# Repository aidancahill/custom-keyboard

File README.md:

# custom-keyboard

A 54-key split ergonomic keyboard with analog joysticks, shift register matrix scanning, and a Seeeduino XIAO nRF52840 BLE microcontroller. Designed from scratch using Ergogen, KiCad, and ZMK firmware.

## Features

- 54 Kailh Choc V1 low-profile keys with hotswap sockets
- Split ergonomic layout with column stagger and splay
- 2× analog joysticks (mouse movement + scroll)
- 74HC595 shift registers for column scanning (3× SIPO)
- 74HC165 shift register for row reading (1× PISO)
- Seeeduino XIAO nRF52840 BLE MCU
- 3D printed case with integrated bottom plate and heat-set inserts
- Custom Grogu silkscreen art

## Layout

```
Left half:                              Right half:
+---+---+---+---+---+---+              +---+---+---+---+---+---+
|Esc| 1 | 2 | 3 | 4 | 5 |              | 6 | 7 | 8 | 9 | 0 |Bks|
+---+---+---+---+---+---+              +---+---+---+---+---+---+
|Tab| Q | W | E | R | T |              | Y | U | I | O | P | \ |
+---+---+---+---+---+---+---+      +---+---+---+---+---+---+---+
| ` | A | S | D | F | G |Alt|      |Alt| H | J | K | L | ; | ' |
+---+---+---+---+---+---+---+      +---+---+---+---+---+---+---+
    | Z | X | C | V | B |              | N | M | , | . | / |
    +---+---+---+---+---+              +---+---+---+---+---+
            |Ctl|Shf|Spc|              |Fn |Shf|Ent|
            +---+---+---+              +---+---+---+

Fn Layer (hold Fn):
+---+---+---+---+---+---+              +---+---+---+---+---+---+
|F1 |F2 |F3 |F4 |F5 |F6 |              |F7 |F8 |F9 |F10|F11|F12|
+---+---+---+---+---+---+              +---+---+---+---+---+---+
| ~ | ! | @ | # | $ | % |              | ^ | & | * | ( | ) |Del|
+---+---+---+---+---+---+---+      +---+---+---+---+---+---+---+
|   | - | = | [ | ] | \ |   |      |   | ↓ | ← | ↑ | → |   |   |
+---+---+---+---+---+---+---+      +---+---+---+---+---+---+---+
    | _ | + | { | } | | |              |Hom|PgD|PgU|End|   |
    +---+---+---+---+---+              +---+---+---+---+---+
            |   |   |   |              |Fn |   |   |
            +---+---+---+              +---+---+---+

Shifted Symbols (Shift + key):
+---+---+---+---+---+---+              +---+---+---+---+---+---+
|   | ! | @ | # | $ | % |              | ^ | & | * | ( | ) |   |
+---+---+---+---+---+---+              +---+---+---+---+---+---+
|   |   |   |   |   |   |              |   |   |   |   |   | | |
+---+---+---+---+---+---+---+      +---+---+---+---+---+---+---+
| ~ |   |   |   |   |   |   |      |   |   |   |   |   | : | " |
+---+---+---+---+---+---+---+      +---+---+---+---+---+---+---+
    |   |   |   |   |   |              |   |   | < | > | ? |
    +---+---+---+---+---+              +---+---+---+---+---+
            |   |   |   |              |   |   |   |
            +---+---+---+              +---+---+---+
```

## Joystick Controls

| Joystick | Axis | Function |
|----------|------|----------|
| Right | Move | Mouse cursor |
| Right | Click | Left click |
| Left | Move | Scroll |
| Left | Click | Right click |

## Repository Structure

```
custom-keyboard/
├── pcb/                  KiCad schematic, PCB, and gerbers
├── case/
│   └── stl/              Print-ready STL file
├── ergogen/              Original Ergogen layout config
├── firmware/             Link to ZMK firmware repo
└── docs/                 Build guide, BOM, and photos
```

## Quick Start

1. **Order PCBs** — upload `pcb/gerbers/` to JLCPCB or PCBWay (2-layer, 1.6mm, any color)
2. **Order components** — see [BOM](docs/bom.md)
3. **3D print case** — slice `case/stl/case_3mm_bottom.stl` (PETG, 50% infill)
4. **Solder** — follow the [build guide](docs/build_guide.md)
5. **Flash firmware** — see [firmware/README.md](firmware/README.md)

## Pin Mapping

| XIAO Pin | Function |
|----------|----------|
| D0 (A0) | Left Joystick Vertical (ADC) |
| D1 (A1) | Left Joystick Horizontal (ADC) |
| D2 (A2) | Right Joystick Vertical (ADC) |
| D3 (A3) | Right Joystick Horizontal (ADC) |
| D4 | Left Joystick Button |
| D5 | Right Joystick Button |
| D6 | 74HC165 PL (parallel load) |
| D7 | 74HC595 RCLK (latch) |
| D8 | SCK (shared SPI clock) |
| D9 | MISO (74HC165 serial data) |
| D10 | MOSI (74HC595 serial data) |

## Matrix Architecture

The keyboard uses a 14-column × 5-row matrix:

- **Columns** are driven by 3× daisy-chained 74HC595 shift registers (serial-in, parallel-out) via SPI MOSI
- **Rows** are read by 1× 74HC165 shift register (parallel-in, serial-out) via SPI MISO
- **Diodes** (1N4148W SOD-123) prevent ghosting, oriented column-to-row
- All shift registers share the SPI clock (SCK), with separate CS/latch pins

## Firmware

ZMK firmware lives in a separate repo: **[custom-keyboard ZMK firmware](https://github.com/aidancahill/custom-keyboard-zmk-firmware)**

Custom ZMK modules include:

- `zmk,gpio-165` — 74HC165 PISO shift register GPIO input driver
- `zmk,input-analog-joystick` — analog joystick pointing device driver

## Design Tools

- **Layout**: [Ergogen](https://ergogen.xyz)
- **PCB**: [KiCad 7](https://www.kicad.org)
- **Routing**: [FreeRouting](https://freerouting.org)
- **Case**: [OpenJSCAD](https://openjscad.xyz)
- **Firmware**: [ZMK](https://zmk.dev)

## Resources & Acknowledgments

| Resource | Description |
|----------|-------------|
| [Ergogen Web UI](https://ergogen.cache.works/) | Browser-based Ergogen layout editor |
| [Ergogen](https://github.com/ergogen/ergogen) | Ergonomic keyboard generator framework |
| [Cantor Keyboard](https://github.com/diepala/cantor) | Split keyboard reference design |
| [Triboard](https://github.com/tarneaux/triboard) | Split keyboard reference design |
| [Kiai Split](https://github.com/makgyber/kiai-split) | Split keyboard reference design |
| [Awesome Split Keyboards](https://github.com/diimdeep/awesome-split-keyboards) | Curated list of split keyboard projects |
| [TOTEM Keyboard](https://github.com/GEIGEIGEIST/TOTEM) | Split keyboard with XIAO BLE support |
| [FlatFootFox](https://flatfootfox.com/) | Ergogen and keyboard design tutorials |
| [Getting Started with Keyboard PCBs](https://brianlow.notion.site/Getting-Started-5c18955a43044c5f98100212e83c19ef) | PCB design guide for keyboards |
| [The Keyboard Matrix](https://www.dairequinlan.com/2020/12/the-keyboard-part-2-the-matrix/) | How keyboard matrices work |
| [74HC595 Shift Register Tutorial](https://lastminuteengineers.com/74hc595-shift-register-arduino-tutorial) | 74HC595 wiring and code tutorial |
| [74HC595 Keyboard Build](https://mehmedbasic.dk/post/74hc595-keyboard/) | Using shift registers in keyboards |
| [Keyboard Layout Editor](https://www.keyboard-layout-editor.com/#/) | Visual keyboard layout designer |

## License

MIT

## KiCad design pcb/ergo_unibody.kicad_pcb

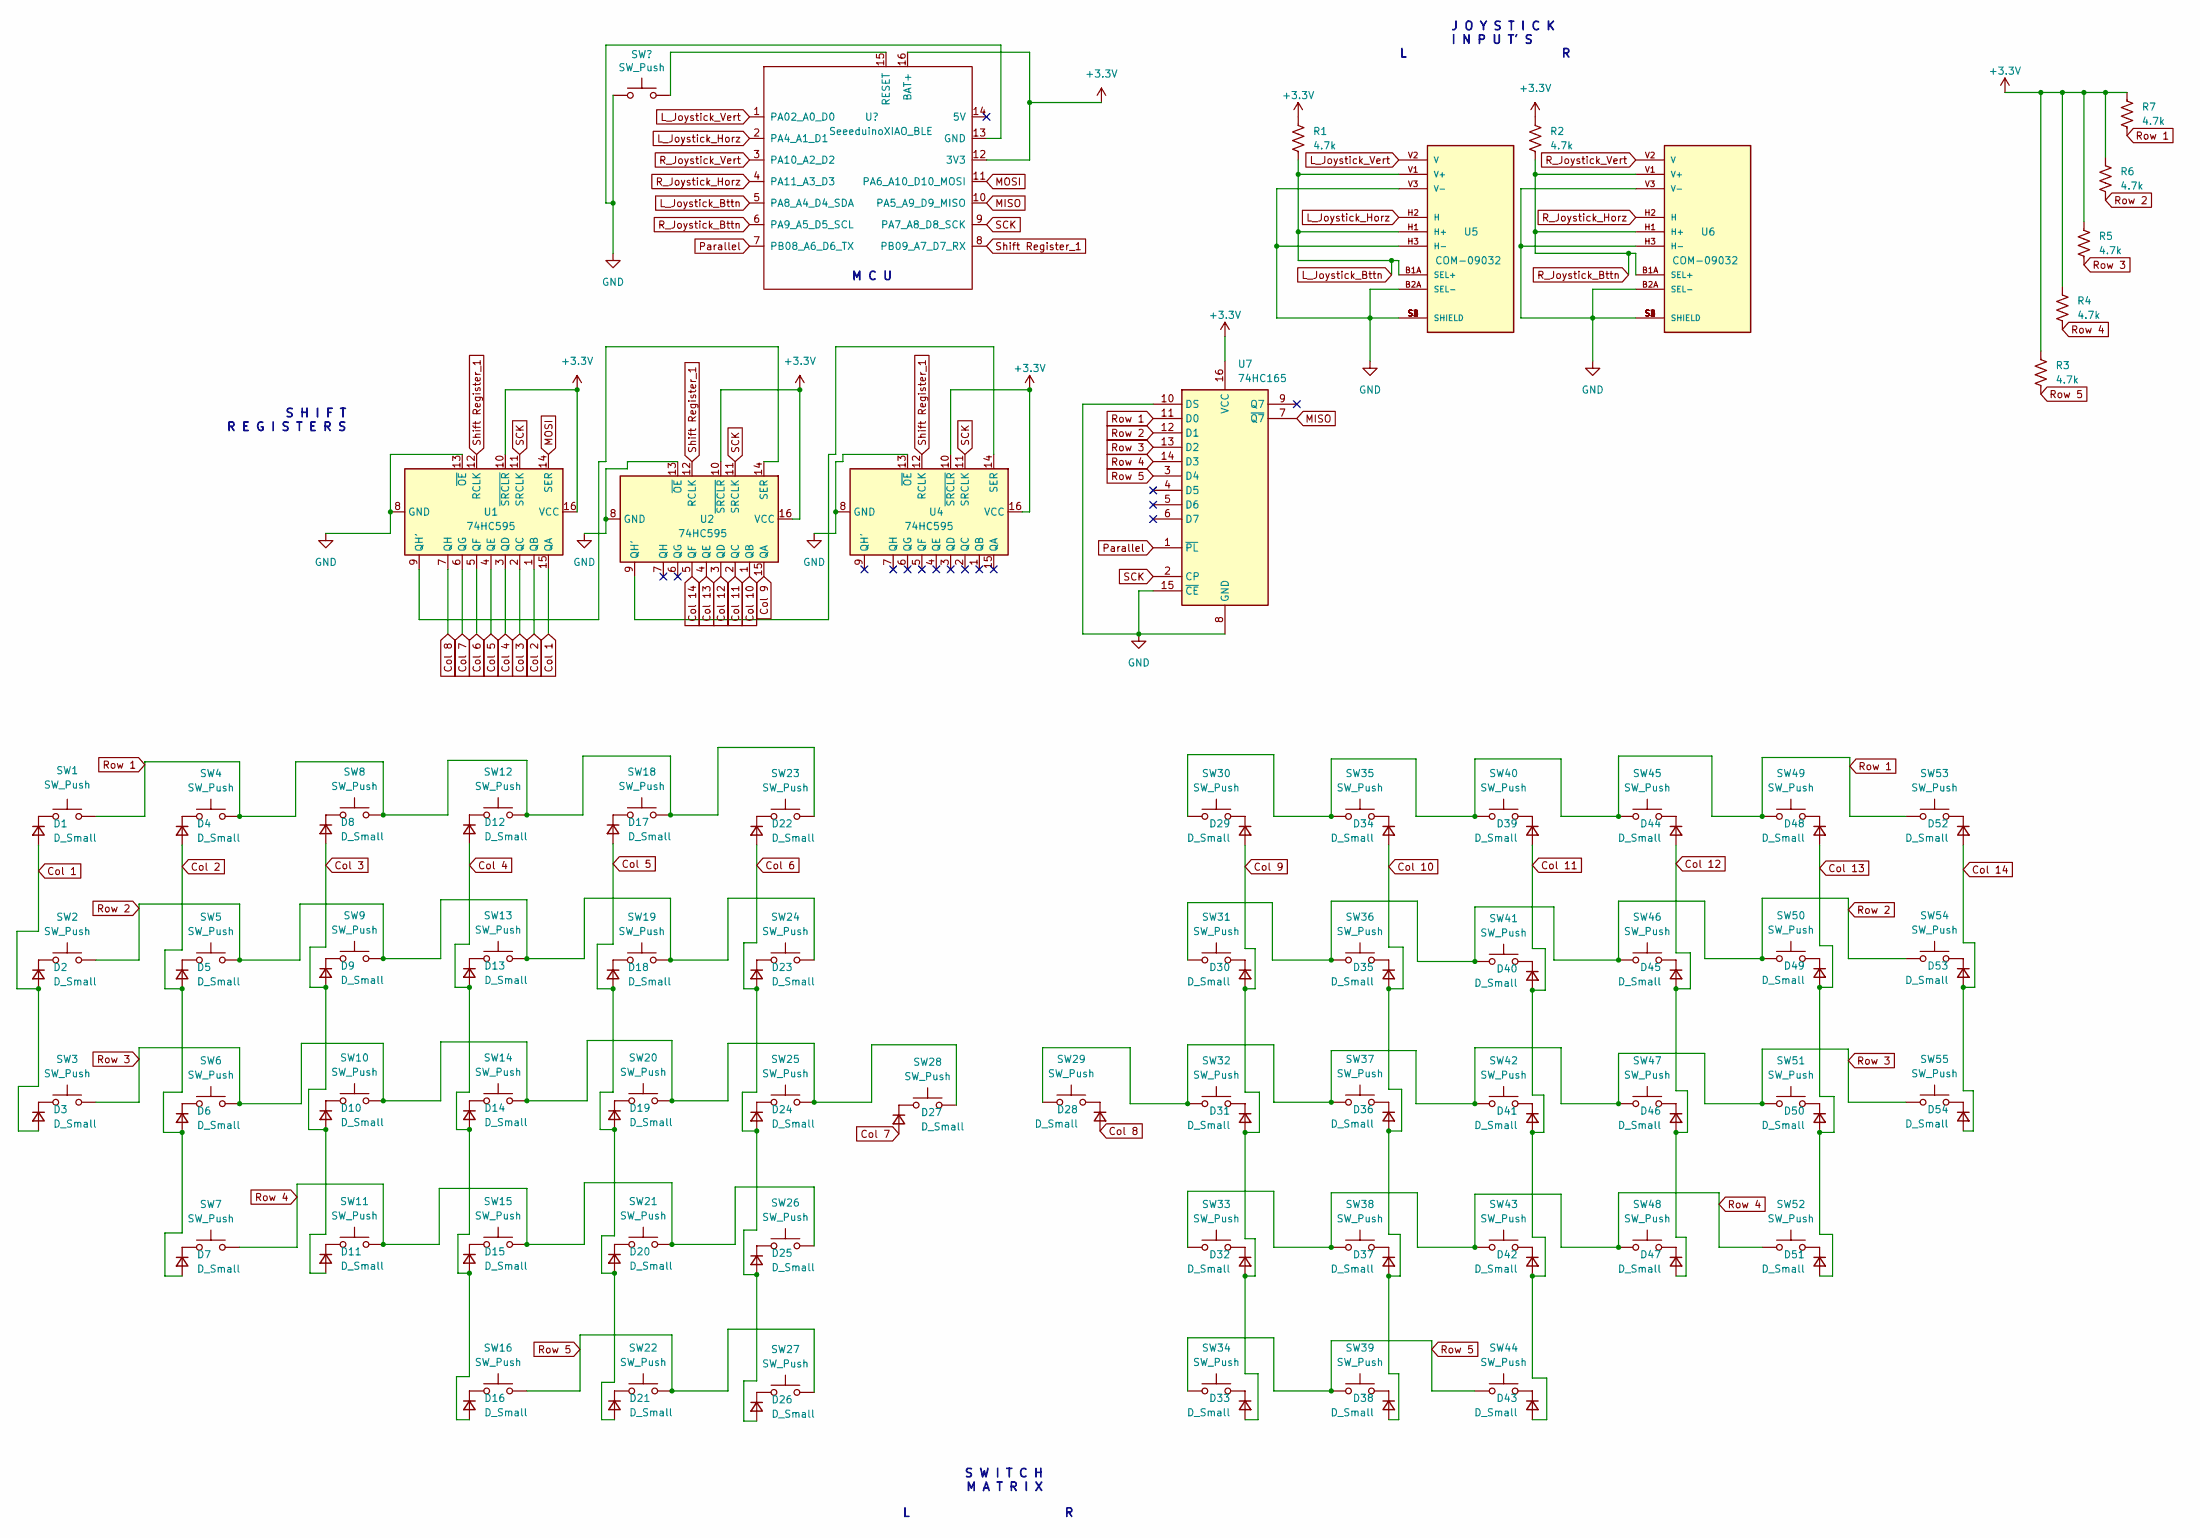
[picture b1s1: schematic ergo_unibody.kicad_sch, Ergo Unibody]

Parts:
D1, D2, D3, D4, D5, D6, D7, D8, D9, D10, D11, D12, D13, D14, D15, D16, D17, D18, D19, D20, D21, D22, D23, D24, D25, D26, D27, D28, D29, D30, D31, D32, D33, D34, D35, D36, D37, D38, D39, D40, D41, D42, D43, D44, D45, D46, D47, D48, D49, D50, D51, D52, D53, D54: D_Small; Diode_SOD123
R1, R2, R3, R4, R5, R6, R7: 4.7k; R_0805_2012Metric
SW1, SW2, SW3, SW4, SW5, SW6, SW7, SW8, SW9, SW10, SW11, SW12, SW13, SW14, SW15, SW16, SW18, SW19, SW20, SW21, SW22, SW23, SW24, SW25, SW26, SW27, SW28, SW29, SW30, SW31, SW32, SW33, SW34, SW35, SW36, SW37, SW38, SW39, SW40, SW41, SW42, SW43, SW44, SW45, SW46, SW47, SW48, SW49, SW50, SW51, SW52, SW53, SW54, SW55: SW_Push; Kailh_socket_PG1350_optional
SW17: SW_Push; SW_SPST_TL3342; LCSC Part Number C79174
U1, U2, U4: 74HC595; SOIC-16_3.9x9.9mm_P1.27mm
U3: SeeeduinoXIAO_BLE; xiao-ble-smd-cutout
U5, U6: COM-09032; XDCR_COM-09032; PARTREV N/A
U7: 74HC165; SOIC-16_3.9x9.9mm_P1.27mm

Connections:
+3.3V: R1.1, R2.1, R3.1, R4.1, R5.1, R6.1, R7.1, U1.10 (~SRCLR), U1.16 (VCC), U2.10 (~SRCLR), U2.16 (VCC), U3.12 (3V3), U3.16 (BAT+), U4.10 (~SRCLR), U4.16 (VCC), U7.16 (VCC)
Col 1: D1.2 (A), D2.2 (A), D3.2 (A), U1.15 (QA)
Col 2: D4.2 (A), D5.2 (A), D6.2 (A), D7.2 (A), U1.1 (QB)
Col 3: D8.2 (A), D9.2 (A), D10.2 (A), D11.2 (A), U1.2 (QC)
Col 4: D12.2 (A), D13.2 (A), D14.2 (A), D15.2 (A), D16.2 (A), U1.3 (QD)
Col 5: D17.2 (A), D18.2 (A), D19.2 (A), D20.2 (A), D21.2 (A), U1.4 (QE)
Col 6: D22.2 (A), D23.2 (A), D24.2 (A), D25.2 (A), D26.2 (A), U1.5 (QF)
Col 7: D27.2 (A), U1.6 (QG)
Col 8: D28.2 (A), U1.7 (QH)
Col 9: D29.2 (A), D30.2 (A), D31.2 (A), D32.2 (A), D33.2 (A), U2.15 (QA)
Col 10: D34.2 (A), D35.2 (A), D36.2 (A), D37.2 (A), D38.2 (A), U2.1 (QB)
Col 11: D39.2 (A), D40.2 (A), D41.2 (A), D42.2 (A), D43.2 (A), U2.2 (QC)
Col 12: D44.2 (A), D45.2 (A), D46.2 (A), D47.2 (A), U2.3 (QD)
Col 13: D48.2 (A), D49.2 (A), D50.2 (A), D51.2 (A), U2.4 (QE)
Col 14: D52.2 (A), D53.2 (A), D54.2 (A), U2.5 (QF)
GND: SW17.2, U1.8 (GND), U1.13 (~OE), U2.8 (GND), U2.13 (~OE), U3.13 (GND), U4.8 (GND), U4.13 (~OE), U5.B2A (SEL-), U5.H3 (H-), U5.S1 (SHIELD), U5.S2 (SHIELD), U5.S3 (SHIELD), U5.S4 (SHIELD), U5.V3 (V-), U6.B2A (SEL-), U6.H3 (H-), U6.S1 (SHIELD), U6.S2 (SHIELD), U6.S3 (SHIELD), U6.S4 (SHIELD), U6.V3 (V-), U7.8 (GND), U7.10 (DS), U7.15 (~CE)
L_Joystick_Bttn: R1.2, U3.5 (PA8_A4_D4_SDA), U5.B1A (SEL+), U5.H1 (H+), U5.V1 (V+)
L_Joystick_Horz: U3.2 (PA4_A1_D1), U5.H2 (H)
L_Joystick_Vert: U3.1 (PA02_A0_D0), U5.V2 (V)
MISO: U3.10 (PA5_A9_D9_MISO), U7.7 (~Q7)
MOSI: U1.14 (SER), U3.11 (PA6_A10_D10_MOSI)
unnamed: D1.1 (K), SW1.1
unnamed: D2.1 (K), SW2.1
unnamed: D3.1 (K), SW3.1
unnamed: D4.1 (K), SW4.1
unnamed: D5.1 (K), SW5.1
unnamed: D6.1 (K), SW6.1
unnamed: D7.1 (K), SW7.1
unnamed: D8.1 (K), SW8.1
unnamed: D9.1 (K), SW9.1
unnamed: D10.1 (K), SW10.1
unnamed: D11.1 (K), SW11.1
unnamed: D12.1 (K), SW12.1
unnamed: D13.1 (K), SW13.1
unnamed: D14.1 (K), SW14.1
unnamed: D15.1 (K), SW15.1
unnamed: D16.1 (K), SW16.1
unnamed: D17.1 (K), SW18.1
unnamed: D18.1 (K), SW19.1
unnamed: D19.1 (K), SW20.1
unnamed: D20.1 (K), SW21.1
unnamed: D21.1 (K), SW22.1
unnamed: D22.1 (K), SW23.1
unnamed: D23.1 (K), SW24.1
unnamed: D24.1 (K), SW25.1
unnamed: D25.1 (K), SW26.1
unnamed: D26.1 (K), SW27.1
unnamed: D27.1 (K), SW28.1
unnamed: D28.1 (K), SW29.1
unnamed: D29.1 (K), SW30.1
unnamed: D30.1 (K), SW31.1
unnamed: D31.1 (K), SW32.1
unnamed: D32.1 (K), SW33.1
unnamed: D33.1 (K), SW34.1
unnamed: D34.1 (K), SW35.1
unnamed: D35.1 (K), SW36.1
unnamed: D36.1 (K), SW37.1
unnamed: D37.1 (K), SW38.1
unnamed: D38.1 (K), SW39.1
unnamed: D39.1 (K), SW40.1
unnamed: D40.1 (K), SW41.1
unnamed: D41.1 (K), SW42.1
unnamed: D42.1 (K), SW43.1
unnamed: D43.1 (K), SW44.1
unnamed: D44.1 (K), SW45.1
unnamed: D45.1 (K), SW46.1
unnamed: D46.1 (K), SW47.1
unnamed: D47.1 (K), SW48.1
unnamed: D48.1 (K), SW49.1
unnamed: D49.1 (K), SW50.1
unnamed: D50.1 (K), SW51.1
unnamed: D51.1 (K), SW52.1
unnamed: D52.1 (K), SW53.1
unnamed: D53.1 (K), SW54.1
unnamed: D54.1 (K), SW55.1
unnamed: U1.9 (QH'), U2.14 (SER)
unnamed: U2.9 (QH'), U4.14 (SER)
unnamed: SW17.1, U3.15 (RESET)
Parallel: U3.7 (PB08_A6_D6_TX), U7.1 (~PL)
R_Joystick_Bttn: R2.2, U3.6 (PA9_A5_D5_SCL), U6.B1A (SEL+), U6.H1 (H+), U6.V1 (V+)
R_Joystick_Horz: U3.4 (PA11_A3_D3), U6.H2 (H)
R_Joystick_Vert: U3.3 (PA10_A2_D2), U6.V2 (V)
Row 1: R7.2, SW1.2, SW4.2, SW8.2, SW12.2, SW18.2, SW23.2, SW30.2, SW35.2, SW40.2, SW45.2, SW49.2, SW53.2, U7.11 (D0)
Row 2: R6.2, SW2.2, SW5.2, SW9.2, SW13.2, SW19.2, SW24.2, SW31.2, SW36.2, SW41.2, SW46.2, SW50.2, SW54.2, U7.12 (D1)
Row 3: R5.2, SW3.2, SW6.2, SW10.2, SW14.2, SW20.2, SW25.2, SW28.2, SW29.2, SW32.2, SW37.2, SW42.2, SW47.2, SW51.2, SW55.2, U7.13 (D2)
Row 4: R4.2, SW7.2, SW11.2, SW15.2, SW21.2, SW26.2, SW33.2, SW38.2, SW43.2, SW48.2, SW52.2, U7.14 (D3)
Row 5: R3.2, SW16.2, SW22.2, SW27.2, SW34.2, SW39.2, SW44.2, U7.3 (D4)
SCK: U1.11 (SRCLK), U2.11 (SRCLK), U3.9 (PA7_A8_D8_SCK), U4.11 (SRCLK), U7.2 (CP)
Shift Register_1: U1.12 (RCLK), U2.12 (RCLK), U3.8 (PB09_A7_D7_RX), U4.12 (RCLK)

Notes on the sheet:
M C U
L R
J O Y S T I C K I N P U T' S L R
S H I F T R E G I S T E R S
S W I T C H M A T R I X

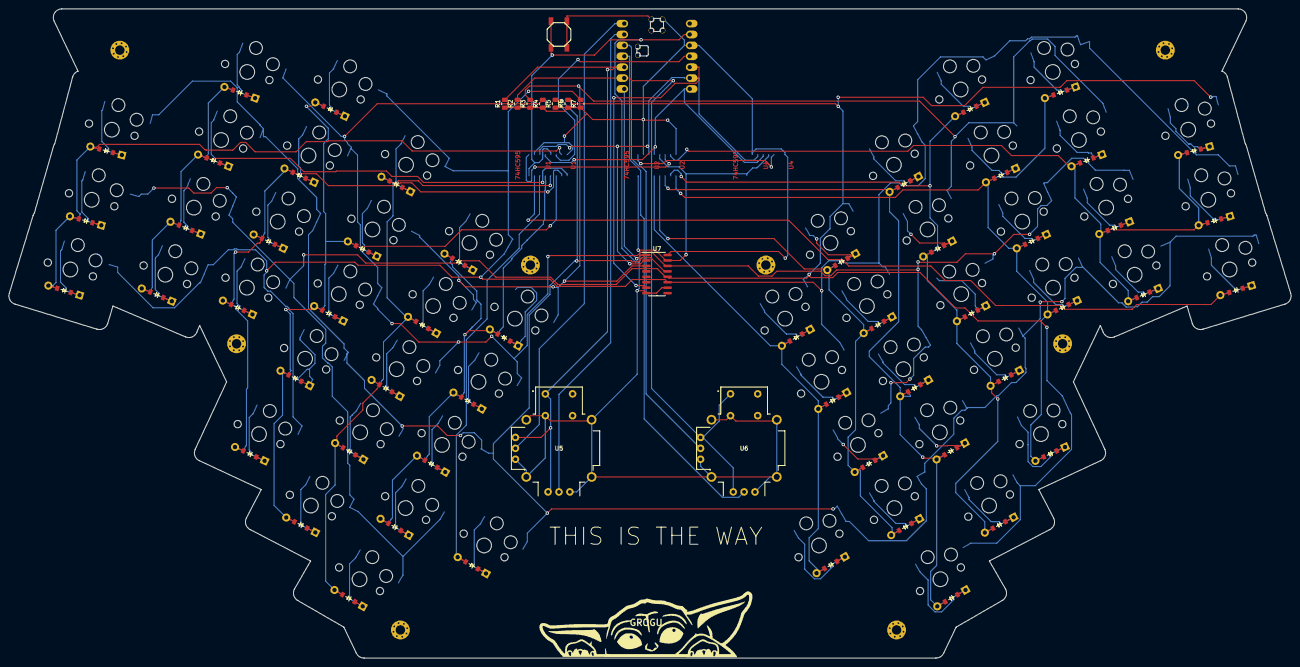
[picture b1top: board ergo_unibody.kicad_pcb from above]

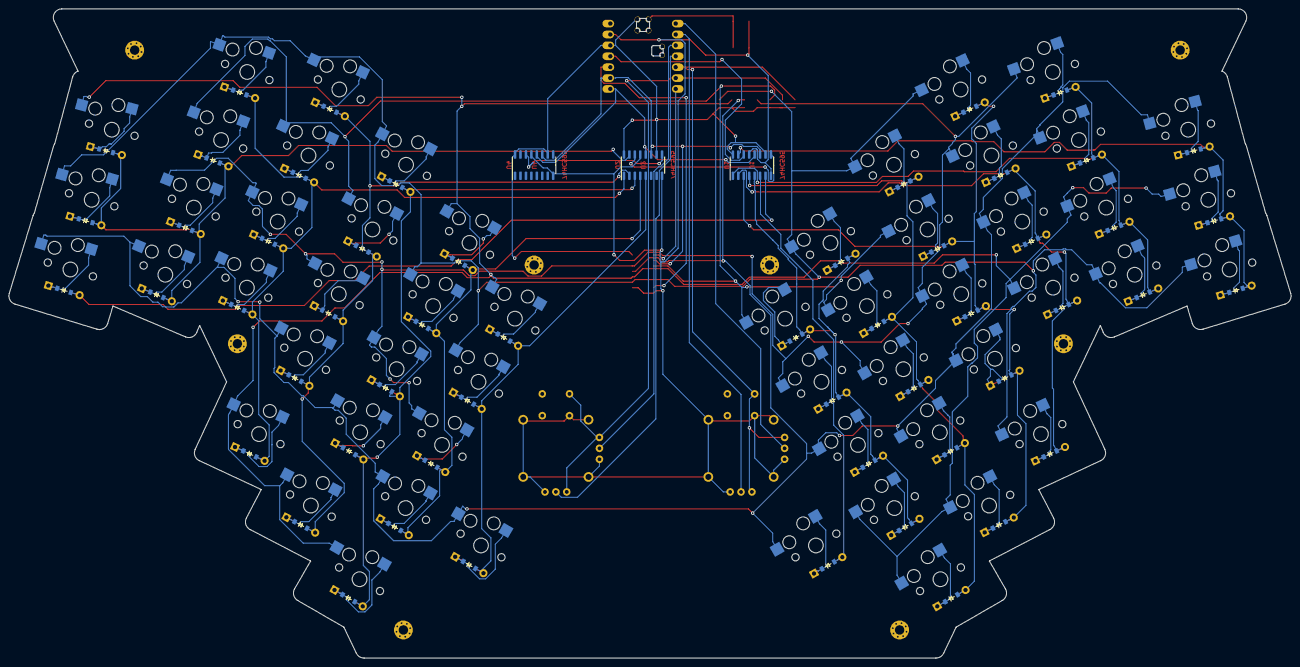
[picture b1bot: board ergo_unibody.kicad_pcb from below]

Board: 2 copper layers, 299.0 x 151.4 mm, 132 parts (3 on the bottom side), 89 nets.

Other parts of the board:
GROGU: LOGO; grogu_mod
_1, _2, _3, _4, _5, _6, _7, _8: MountingHole_2.2mm_M2_Pad_Via

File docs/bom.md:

# Bill of Materials

## Electronics

| Qty | Component | Package | Part Number | Source | Est. Price |
|-----|-----------|---------|-------------|--------|------------|
| 54 | Kailh Choc V1 hotswap sockets | — | — | LowproKB | $10.50 |
| 60 | Ambients Silent Twilight switches (or any Choc V1) | PG1350 | — | LowproKB | $78.00 |
| 54 | MBK 1u keycaps | Choc V1 | — | LowproKB | $21.00 × 6 |
| 2 | MBK homing keycaps | Choc V1 | — | LowproKB | $1.10 |
| 54 | 1N4148W diodes | SOD-123 | 1N4148W-13-F | DigiKey | ~$5 |
| 3 | 74HC595 shift registers | SOIC-16 | SN74HC595DR | DigiKey | ~$3 |
| 1 | 74HC165 shift register | SOIC-16 | SN74HC165DR | DigiKey | ~$1 |
| 7 | 10kΩ resistors | 0805 SMD | — | Amazon | $5 |
| 1 | Seeeduino XIAO nRF52840 BLE (pre-soldered) | — | 102010631-FA | Amazon | $18 |
| 2 | COM-09032 joysticks | — | COM-09032 | SparkFun | ~$10 |
| 1 | TL3342 reset button | SMD | — | DigiKey | ~$1 |
| 2 | 7-pin 2.54mm female header sockets | Through-hole | — | Amazon | $9 (25-pack) |

## Hardware

| Qty | Component | Spec | Source | Est. Price |
|-----|-----------|------|--------|------------|
| 8+ | M2 heat-set brass inserts | M2 × 4mm | Amazon (ruthex) | ~$8 (70-pack) |
| 8 | M2 socket head cap screws | M2 × 5mm | Amazon | ~$8 |

## PCB

| Item | Spec |
|------|------|
| Layers | 2 |
| Thickness | 1.6mm |
| Surface finish | HASL or ENIG |
| Solder mask | Any color (black recommended) |
| Silkscreen | White |
| Min track/spacing | 6/6 mil |
| Min hole size | 0.3mm |

Order from JLCPCB or PCBWay. Upload the gerber zip from `pcb/gerbers/`. Minimum order is usually 5 boards.

## 3D Printed Case

| Item | File | Material | Settings |
|------|------|----------|----------|
| Case (with integrated 3mm bottom) | `case/stl/case_3mm_bottom.stl` | PETG or PLA | 50% infill, 0.2mm layer height |

Print yourself or order from PCBWay's 3D printing service.

## Tools Required

- Soldering iron with fine tip (conical or chisel)
- Tweezers (angled tip preferred)
- Flux (pen or paste)
- Solder wire (0.5-0.8mm diameter, leaded recommended for beginners)
- Solder wick (for fixing mistakes)
- Isopropyl alcohol 91%+ (for cleaning flux)
- Toothbrush (for scrubbing flux)
- Soldering iron (for heat-set inserts)

## Estimated Total Cost

| Category | Cost |
|----------|------|
| Switches + keycaps | ~$115 |
| Electronics (diodes, ICs, MCU, headers) | ~$45 |
| PCB (5 pcs) | ~$15-25 |
| 3D printed case | ~$10-30 |
| Hardware (screws, inserts) | ~$16 |
| **Total** | **~$200-230** |

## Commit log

2026-03-30 Initial commit: custom-keyboard hardware project
2026-03-30 Add images and pcb/schematics
2026-03-30 Update README with resources and acknoledgements
2026-03-31 Upload final build photos, and update readme
2026-04-06 Update keymap layout and add shifted symbols reference
